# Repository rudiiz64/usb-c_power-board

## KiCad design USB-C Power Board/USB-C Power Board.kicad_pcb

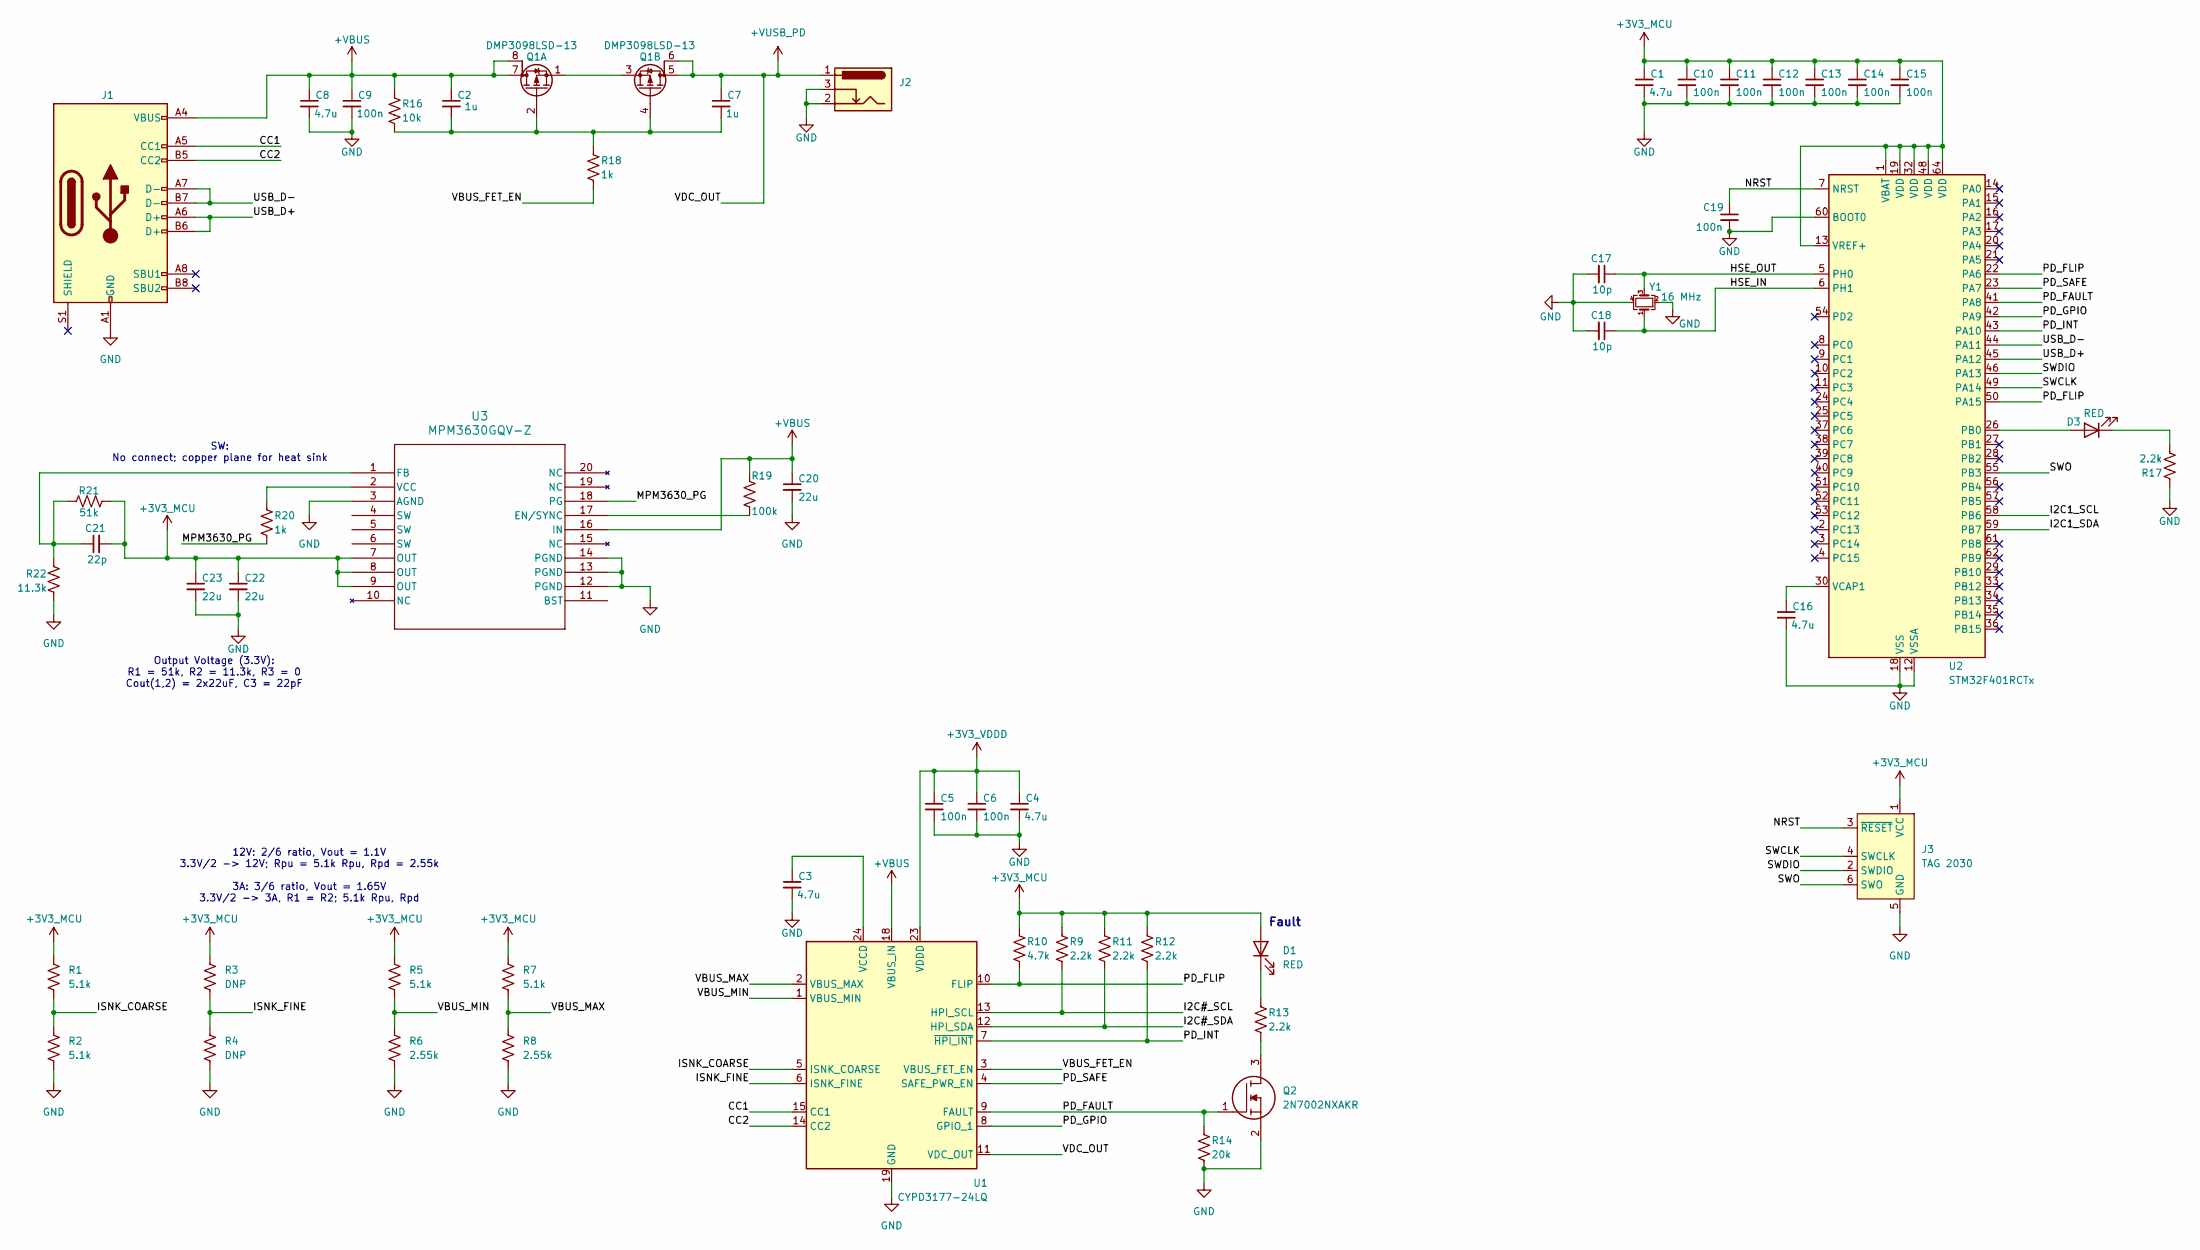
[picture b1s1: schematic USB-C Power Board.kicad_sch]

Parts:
C1, C3, C4, C8, C16: 4.7u; C_0603_1608Metric
C2, C7: 1u; C_0603_1608Metric
C5, C6, C9, C10, C11, C12, C13, C14, C15, C19: 100n; C_0603_1608Metric
C17, C18: 10p; C_0402_1005Metric
C20, C22, C23: 22u; C_0603_1608Metric
C21: 22p; C_0402_1005Metric
D1, D3: RED; D_0402_1005Metric
J1: USB_C_Receptacle_USB2.0_16P; USB_C_Receptacle_GCT_USB4110
J2: Barrel_Jack_Switch; CUI_PJ-050AH
J3: TAG 2030; Tag-Connect_TC2030-IDC-FP_2x03_P1.27mm_Vertical
Q1: DMP3098LSD-13; SOIC127P600X175-8N
Q2: 2N7002NXAKR; SOT95P230X110-3N; Mouser Part Number 771-2N7002NXAKR
R1, R2, R5, R7: 5.1k; R_0603_1608Metric
R3, R4: DNP; R_0603_1608Metric
R6, R8: 2.55k; R_0603_1608Metric
R9, R11, R12, R13, R17: 2.2k; R_0603_1608Metric
R10: 4.7k; R_0603_1608Metric
R14: 20k; R_0603_1608Metric
R16: 10k; R_0603_1608Metric
R18, R20: 1k; R_0603_1608Metric
R19: 100k; R_0603_1608Metric
R21: 51k; R_0603_1608Metric
R22: 11.3k; R_0603_1608Metric
U1: CYPD3177-24LQ; QFN-24-1EP_4x4mm_P0.5mm_EP2.75x2.75mm
U2: STM32F401RCTx; LQFP-64_10x10mm_P0.5mm
U3: MPM3630GQV-Z; QFN3p0x5p0x1p6_MPM3630_MNP
Y1: 16 MHz; Crystal_SMD_SeikoEpson_FA128-4Pin_2.0x1.6mm

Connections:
+3V3_MCU: C1.1, C10.1, C11.1, C12.1, C13.1, C14.1, C15.1, C21.2, C22.1, C23.1, D1.2 (A), J3.1 (VCC), R1.1, R3.1, R5.1, R7.1, R9.1, R10.1, R11.1, R12.1, R21.2, U2.1 (VBAT), U2.13 (VREF+), U2.19 (VDD), U2.32 (VDD), U2.48 (VDD), U2.64 (VDD), U3.7 (OUT), U3.8 (OUT), U3.9 (OUT)
+3V3_VDDD: C4.1, C5.1, C6.1, U1.23 (VDDD)
+VBUS: C2.1, C8.1, C9.1, C20.1, J1.A4 (VBUS), J1.A9 (VBUS), J1.B4 (VBUS), J1.B9 (VBUS), Q1.7 (D), Q1.8 (G), R16.1, R19.1, U1.18 (VBUS_IN), U3.16 (IN)
+VUSB_PD: C7.1, J2.1, Q1.5 (D), Q1.6 (G), U1.11 (VDC_OUT)
/CC1: J1.A5 (CC1), U1.15 (CC1)
/CC2: J1.B5 (CC2), U1.14 (CC2)
/HSE_IN: C18.1, U2.6 (PH1), Y1.1
/HSE_OUT: C17.1, U2.5 (PH0), Y1.3
/I2C1_SCL: U2.58 (PB6)
/I2C1_SDA: U2.59 (PB7)
/I2C#_SCL: R9.2, U1.13 (HPI_SCL)
/I2C#_SDA: R11.2, U1.12 (HPI_SDA)
/ISNK_COARSE: R1.2, R2.1, U1.5 (ISNK_COARSE)
/ISNK_FINE: R3.2, R4.1, U1.6 (ISNK_FINE)
/MPM3630_PG: R20.2, U3.18 (PG)
/NRST: C19.1, J3.3 (~RESET), U2.7 (NRST)
/PD_FAULT: Q2.1, R14.1, U1.9 (FAULT), U2.41 (PA8)
/PD_FLIP: R10.2, U1.10 (FLIP), U2.22 (PA6), U2.50 (PA15)
/PD_GPIO: U1.8 (GPIO_1), U2.42 (PA9)
/PD_INT: R12.2, U1.7 (~HPI_INT), U2.43 (PA10)
/PD_SAFE: U1.4 (SAFE_PWR_EN), U2.23 (PA7)
/SWCLK: J3.4 (SWCLK), U2.49 (PA14)
/SWDIO: J3.2 (SWDIO), U2.46 (PA13)
/SWO: J3.6 (SWO), U2.55 (PB3)
/USB_D+: J1.A6 (D+), J1.B6 (D+), U2.45 (PA12)
/USB_D-: J1.A7 (D-), J1.B7 (D-), U2.44 (PA11)
/VBUS_FET_EN: R18.2, U1.3 (VBUS_FET_EN)
/VBUS_MAX: R7.2, R8.1, U1.2 (VBUS_MAX)
/VBUS_MIN: R5.2, R6.1, U1.1 (VBUS_MIN)
GND: C1.2, C3.2, C4.2, C5.2, C6.2, C8.2, C9.2, C10.2, C11.2, C12.2, C13.2, C14.2, C15.2, C16.2, C17.2, C18.2, C19.2, C20.2, C22.2, C23.2, J1.A1 (GND), J1.A12 (GND), J1.B1 (GND), J1.B12 (GND), J2.2, J2.3, J3.5 (GND), Q2.2, R2.2, R4.2, R6.2, R8.2, R14.2, R17.1, R22.2, U1.19 (GND), U1.22 (GND), U1.25 (GND), U2.12 (VSSA), U2.18 (VSS), U2.31 (VSS), U2.47 (VSS), U2.60 (BOOT0), U2.63 (VSS), U3.3 (AGND), U3.12 (PGND), U3.13 (PGND), U3.14 (PGND), Y1.2, Y1.4
unnamed: C2.2, C7.2, Q1.2 (G), Q1.4 (G), R16.2, R18.1
unnamed: D1.1 (K), R13.1
unnamed: D3.2 (A), U2.26 (PB0)
unnamed: D3.1 (K), R17.2
unnamed: Q1.1 (S), Q1.3 (S)
unnamed: Q2.3, R13.2
unnamed: C3.1, U1.24 (VCCD)
unnamed: C16.1, U2.30 (VCAP1)
unnamed: R19.2, U3.17 (EN/SYNC)
unnamed: C21.1, R21.1, R22.1, U3.1 (FB)
unnamed: R20.1, U3.2 (VCC)

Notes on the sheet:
SW: No connect; copper plane for heat sink
12V: 2/6 ratio, Vout = 1.1V 3.3V/2 -> 12V; Rpu = 5.1k Rpu, Rpd = 2.55k 3A: 3/6 ratio, Vout = 1.65V 3.3V/2 -> 3A, R1 = R2; 5.1k Rpu, Rpd
Output Voltage (3.3V): R1 = 51k, R2 = 11.3k, R3 = 0 Cout(1,2) = 2x22uF, C3 = 22pF
Fault

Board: 2 copper layers, 55 parts (0 on the bottom side), 39 nets, no tracks yet.

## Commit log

2024-03-19 Rev A
    + Finalized initial schematic
    + Included datasheet specific calculations
    + Began component placement
